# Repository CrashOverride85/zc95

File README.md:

# ZC95

**Note**: This repo has submodules, so if cloning, it's best to use the recursive option.

## Introduction
The ZC95 is a DIY four channel EStim box with similar output design and feel to the MK312-BT (which in turn is a clone of the ET-312B).

![zc95]

The box is primarily intended for standalone use (i.e. not used whilst connected to phone/laptop/tablet), but can be controlled remotely via a Python GUI, and run Lua scripts that have been uploaded to it over serial or WiFi.

Main features:
- 4 isolated channels 
- [Audio input](./docs/AudioInput-Operation.md) - line level for estim tracks or microphone input (selectable via menu)
- [Many inbuilt patterns](./docs/Patterns.md) - around 14, not counting audio and more esoteric stuff
- Custom patterns can be written in [Lua](./docs/LuaNotes.md)
- Two stereo 3.5mm trigger input sockets, allowing for up to 4 external inputs (e.g. remote buttons, foot pedals, etc.)
- Support for many [BLE remote/camera buttons](./docs//BluetoothPeripherals.md), e.g. to trigger output when the button is pressed
- [Remote control](./docs/RemoteAccess.md) over WiFi or serial using a python app
- Allows limited control of a certain type of 433MHz shock collar
- Somewhat experimental [BLE steaming](./docs/BleStreaming.md) - allows for per-pulse level control from laptop or other device, with an example in python
- An accessory port with 3 output lines that can be controlled from Lua scripts, to allow interacting with other devices

Technical details:
- Has been designed with the JLC PCB assembly service in mind, and is mostly an SMD design with a few though hole parts
- Uses 2x Raspberry Picos
- Firmware is open source and mostly C++, and makes use of many [3rd party libraries](./docs/Credits.md)
- 26650 cell for power
- KiCad project files included in repo, not just gerbers
- Audio input includes microphone preamp that can be toggled via menu, along with variable gain
- Consists of 3 PCBs:
   * Front panel - no traces, just text / mounting holes
   * Front panel controls - 4x POTs and associated ADC, 1x rotary encoder and 6 serial RGB LEDs. Designed for production using the SMT assembly service at JLCPCB, with a handful of extra through hole parts also requiring hand soldering.
   * Main board - power supply / charging, pattern generation, button input, output signal generation, audio input
- Case is either an off the shelf Hammond 1598DBK (larger), or a 3D printed case (step/stl files provided)

## [Build guide](docs/Build.md)

## [Schematics](schematics/)

## [Gerbers](pcb/)

## [Compiled firmware](https://github.com/CrashOverride85/zc95/releases/)

## [Operation notes](docs/Operation.md)

## [Pattern guide](docs/Patterns.md)

## [Lua scripting notes](docs/LuaNotes.md)

## [Notes on building source](docs/SourceBuildNotes.md)

## [Credits](docs/Credits.md)

# Miscellaneous  
## History
The ZC95 is very heavily inspired by the MK312-BT, which is a reversed engineered version of the ET-312. The original repo for that project is long gone, but there is a fork [here](https://github.com/CrashOverride85/mk312-bt).

The [ZC95 mk1](https://github.com/CrashOverride85/zc95/tree/MKI) was made public in late 2021, and had a similar form factor to the MK312. That version has been built successfully by many.

The [ZC95 mk1](https://github.com/CrashOverride85/zc95/tree/MKI) had the output stage on a separate PCB. It's no longer part of the zc95 build, but could still be built and used to add 4 channel estim output to an Arduino (with notes for & tested with an ESP32).
The PCB / BoM / build notes for it are [here](./misc/OutputBoard/README.md).

## MKI vs. MKII
These are the main changes from the MKI to MKII:

 - Much smaller - the mainboard is less than half the size
 - Output, Audio and main board are now combined
 - USB-C charger input instead of 15v barrel jack
 - 26650 cell instead of 12v SLA battery (similar capacity)
 - "Aux" socket swapped for separate "Serial" and "Audio" sockets
 - Output sockets changed from 2.5mm to 3.5mm
 - Serial selectable (via jumpers) between 3.3v TTL and RS232
 - Display no longer briefly flashes white on power on
 - Removed: 12v output on accessory port

## Support, feedback, etc.
The ZC95 project is provided 'as is' without warranty of any kind, either express or implied. The project is provided for your use at your own risk.

Having said that, if you run into difficulties or have questions, the two best places to try are:
- Github [discussions](https://github.com/CrashOverride85/zc95/discussions) or [issues](https://github.com/CrashOverride85/zc95/issues)
- The ZC95 channel on [Joanne's E-Stim Community discord](https://discord.gg/HbGKY2t), see Estim control boxes -> zc95
  - I'd highly recommend joining this discord server anyway, the zc95 chanel is a _tiny_ part of what's there

## Other projects
Other related projects that are worth checking out:

- [NeoDK](https://github.com/Onwrikbaar/NeoDK) - Advanced electrostimulation machine development kit. In active development, and also has a chanel on [Joanne's E-Stim Community discord](https://discord.gg/HbGKY2t)

- MK-312BT - Project the ZC95 was inspired by, and shares lot in common with (original repo gone, but there are many [forks](https://github.com/CrashOverride85/mk312-bt))

- [WT-312](https://github.com/WendyTeslaburger/WT-312) - 312 style driver, intended for integration into other projects

- [FOC-Stim](https://github.com/diglet48/FOC-Stim) - In development, checkout the foc-stim channel on [Joanne's E-Stim Community discord](https://discord.gg/HbGKY2t) for the latest

# TODO
## Firmware
   - Triphase support from Lua 
   - Allow Lua scripts to interact with shock collars
   - Combo pattern? Having, e.g., waves on channels 1+2 plus something like TENS on 3+4 would be good
   - Save pattern settings on exit?
   - Disable when plugged in / switch to charging screen (maybe a setting in the menu to disable)
   - Accessory port doesn't do much - just 3 output lines. There's a serial interface there too, which could be exposed in the Lua environment

## Hardware
   - Improved 3D printed case?

## Known issues
   - Will charge faster if switched on when plugged in, and not switched off for at least 10 seconds (or just left on)
   - Sometimes when finished charging (battery icon showing solid green), the battery percentage will only show ~95% despite being fully charged. Should be fixed in a future firmware version. 

[zc95]: docs/images/powered_up.jpg "Assembled ZC95"

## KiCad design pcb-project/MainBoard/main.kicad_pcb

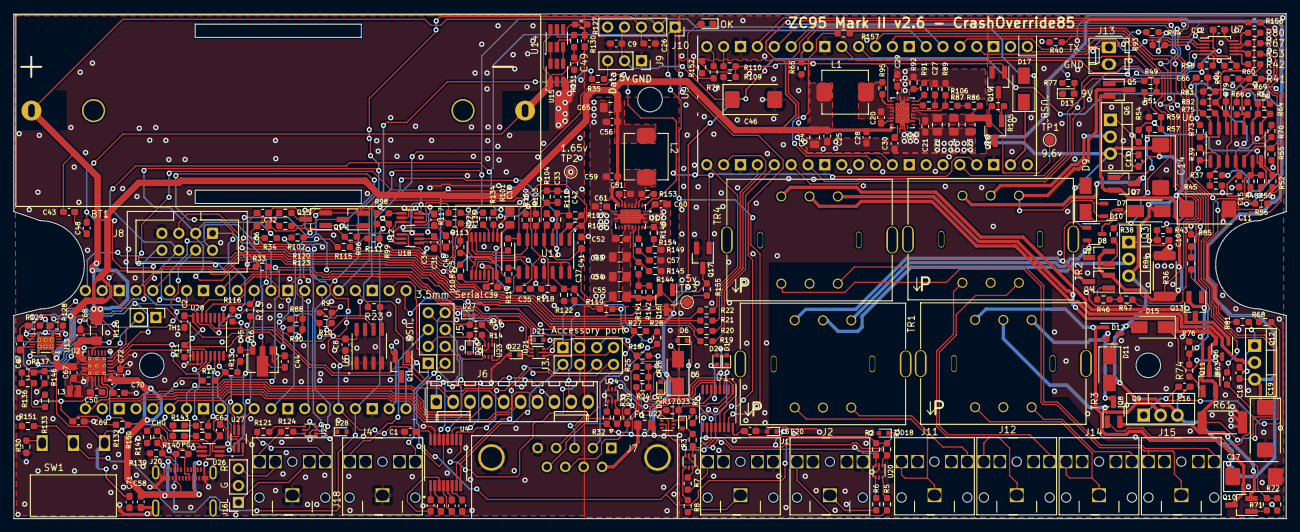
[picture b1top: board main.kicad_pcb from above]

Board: 2 copper layers, 191.5 x 76.0 mm, 334 parts (1 on the bottom side), 263 nets.

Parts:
BT1: 26650 Cell; BH-26650-A5BJ001
C1, C2, C5, C21, C26, C32, C36, C37, C39, C41, C42, C43, C44, C45, C48, C52: 1uF; C_0603_1608Metric_Pad1.08x0.95mm_HandSolder
C3, C4, C6, C7, C8, C10, C12, C13, C15, C16, C18, C20, C28, C30, C31, C34, C49, C51, C59, C61: 100nF; C_0603_1608Metric_Pad1.08x0.95mm_HandSolder
C9, C25, C40, C56, C66, C67, C68, C70, C72: 10uF; C_0603_1608Metric_Pad1.08x0.95mm_HandSolder
C11, C14, C17, C19, C46: 220uF; CP_EIA-7343-43_Kemet-X_Pad2.25x2.55mm_HandSolder
C22, C23, C24, C38, C53, C54, C55, C64, C65: 22uF; C_0805_2012Metric_Pad1.18x1.45mm_HandSolder
C27, C57, C62: 10nF; C_0603_1608Metric_Pad1.08x0.95mm_HandSolder
C29, C33, C35, C60: 3.3nF; C_0603_1608Metric_Pad1.08x0.95mm_HandSolder
C47: 0.47uF; C_0603_1608Metric_Pad1.08x0.95mm_HandSolder
C50: 47nF; C_0603_1608Metric_Pad1.08x0.95mm_HandSolder
C58, C71: DNP; C_0603_1608Metric_Pad1.08x0.95mm_HandSolder
C63: DNP; R_0805_2012Metric_Pad1.20x1.40mm_HandSolder
C69: 4.7uF; C_0603_1608Metric_Pad1.08x0.95mm_HandSolder
D1, D6, D18, D20, D21, D22, D23, D24, D25, D26, D27, D28: BZX584C3V6; D_SOD-523
D3: PG; LED_0603_1608Metric_Pad1.05x0.95mm_HandSolder
D4: CHRG; LED_0603_1608Metric_Pad1.05x0.95mm_HandSolder
D5: 1SMA4734A; D_SMA
D7, D9, D11, D15: SMAJ13A; D_SMA
D8, D10, D12, D16: BAV23CL; SOT-23-3
D13: 9v; LED_0603_1608Metric_Pad1.05x0.95mm_HandSolder
D14: OK; LED_0603_1608Metric_Pad1.05x0.95mm_HandSolder
D17: SS34; D_SMA
F1: 500mA; Fuse_0805_2012Metric_Pad1.15x1.40mm_HandSolder
J1: TRG1; PJ-3062-CO
J2: TRG2; PJ-3062-CO
J3, J5: Conn_02x04_Odd_Even; PinSocket_2x04_P2.54mm_Vertical
J4, J18: AudioJack3_SwitchTR; PJ-3062-CO
J6: LCD; Molex_KK-254_AE-6410-10A_1x10_P2.54mm_Vertical
J7: ACC Port; DSUB-9_Female_Horizontal_P2.77x2.84mm_EdgePinOffset7.70mm_H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
J8: FrontPanel; IDC-Header_2x04_P2.54mm_Vertical
J9: 433TX; PinSocket_1x03_P2.54mm_Vertical
J10: I2C; PinSocket_1x05_P2.54mm_Vertical
J11: CHAN1; PJ-3062-CO
J12: CHAN2; PJ-3062-CO
J13: Conn_01x02; Molex_KK-254_AE-6410-02A_1x02_P2.54mm_Vertical
J14: CHAN3; PJ-3062-CO
J15: CHAN4; PJ-3062-CO
J16: AudioIn; PinSocket_1x03_P2.54mm_Vertical
J20: USB_C_Receptacle; 1054500101
L1, L2: 1.5uH; FXL0630
L3: FTC201610S1R0MBCA; FTC201610S
Q1, Q14, Q15, Q16, Q18: AO3401A; SOT-23_Handsoldering
Q2, Q4, Q5, Q7, Q8, Q10, Q11, Q13, Q17, Q19: AO3400A; SOT-23_Handsoldering
Q3, Q6, Q9, Q12: IRF9Z24NPBF; TO-220-3_Vertical
R1, R2, R3, R4, R11, R15, R17, R18, R23, R24, R25, R26, R33, R34, R38, R43, R46, R49, R54, R57, R63, R68, R71, R74, R77, R81, R84, R101, R103, R105, R109, R114, R117, R125, R128, R129, R132, R136, R137, R146, R151, R152, R155, R156, R157: 10k; R_0603_1608Metric_Pad0.98x0.95mm_HandSolder
R5, R6, R7, R8, R9, R14, R16, R19, R20, R21, R22, R27, R28, R29, R30, R31, R32, R35, R88, R110, R121, R124, R127, R134, R135: 100R; R_0603_1608Metric_Pad0.98x0.95mm_HandSolder
R10, R90, R120, R123, R138, R143: 2k2; R_0603_1608Metric_Pad0.98x0.95mm_HandSolder
R12, R13, R37, R39, R40, R42, R45, R47, R48, R50, R51, R53, R56, R58, R59, R60, R62, R64, R65, R67, R70, R72, R73, R75, R76, R80, R83, R85, R96, R98, R104, R108, R111, R112, R116, R118, R119, R122, R142, R144, R147, R150: 100k; R_0603_1608Metric_Pad0.98x0.95mm_HandSolder
R36, R61: 0.5R; R_2512_6332Metric_Pad1.40x3.35mm_HandSolder
R41, R44, R52, R55, R66, R69, R79, R82, R91, R92, R97, R99, R148, R149: 150k; R_0603_1608Metric_Pad0.98x0.95mm_HandSolder
R78: 1.5k; R_0603_1608Metric_Pad0.98x0.95mm_HandSolder
R86, R95, R141, R153: 330K; R_0603_1608Metric_Pad0.98x0.95mm_HandSolder
R87, R89, R145: 56k; R_0603_1608Metric_Pad0.98x0.95mm_HandSolder
R93, R94, R100, R106, R107, R113, R133, R154: 4k7; R_0603_1608Metric_Pad0.98x0.95mm_HandSolder
R102, R115, R130, R131: 1k; R_0603_1608Metric_Pad0.98x0.95mm_HandSolder
R126: 0.01R; R_1206_3216Metric_Pad1.30x1.75mm_HandSolder
R139, R140: 5.1k; R_0603_1608Metric_Pad0.98x0.95mm_HandSolder
SW1: SW_SPDT; SS-12D06L5
TH1: Thermistor_NTC; PinHeader_1x02_P2.54mm_Vertical
TP1: TestPoint_9.6v; TestPoint_Pad_D1.5mm
TP2: TestPoint_1.65v; TestPoint_Pad_D1.5mm
TP3: TestPoint_5v; TestPoint_Pad_D1.5mm
TR1, TR2, TR3, TR4: 42TL004-RC; 42TL+U
U1, U28: TCA9534; TSSOP-16_4.4x5mm_P0.65mm
U2: BQ25601; Texas_S-PWQFN-N24_EP2.7x2.7mm_ThermalVias
U3, U9: Pico; RPi_Pico_SMD_TH
U4: MAX3232EEAE+T; SOP65P777X199-16N
U5: AT24C04CDRG; SOP-8_3.76x4.96mm_P1.27mm
U6, U11: LM324; SOIC-14_3.9x8.7mm_P1.27mm
U7: MCP4728; MSOP-10_3x3mm_P0.5mm
U8, U17: TPS61088; IC_TPS61088RHLR
U10: MCP4651; TSSOP-14_4.4x5mm_P0.65mm
U12, U18, U26, U27: SN74LVC1G3157DCKR; SOT-363_SC-70-6_Handsoldering
U13: BQ27441-G1; Texas_S-PDSO-N12
U14: HY2111-GB; SOT-23-6_Handsoldering
U15: FS8205A; SOT-23-6_Handsoldering
U16: HT7533-1; SOT-89-3
U19, U20, U21, U22, U23, U24, U25: USBLC6-2P6; SOT-666

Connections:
1.65v: C33.2, C35.2, R97.1, R99.1, R100.2, R104.1, R107.2, R111.1, R112.1, R113.2, R118.1, TP2.1, U11.13 (-), U11.14
3.5v: C25.1, C28.1, C56.1, C59.1, C63.1, C64.2, C65.1, C67.1, C71.1, D3.2 (A), D4.2 (A), D17.2 (A), L1.1, L2.1, L3.2, Q1.3 (D), SW1.1 (A), U2.15 (SYS), U2.16 (SYS), U8.9 (VIN), U17.9 (VIN)
3v3: C1.1, C2.2, C5.2, C8.2, C26.1, C62.1, J8.3, J10.3, R1.1, R2.1, R3.1, R4.1, R10.2, R11.1, R15.1, R17.1, R18.2, R24.1, R25.1, R26.1, R33.2, R34.2, R90.2, U1.16 (VDD), U3.36 (3V3), U4.16 (VCC), U5.8 (VCC), U26.5 (VCC), U27.5 (VCC), U28.16 (VDD)
3v3_2: C12.1, R58.2, R93.2, R94.2, U7.1 (VDD), U9.36 (3V3)
3v3_LDO: C45.2, Q14.2 (S), Q15.2 (S), R116.2, R119.2, U16.3 (VOUT)
5v: C9.1, C31.2, C34.2, C38.1, C39.2, C40.1, C41.2, C42.1, C44.2, C46.1, C66.1, D5.1 (K), F1.1, J6.9, J8.5, J9.2, J10.4, Q16.3 (D), R37.2, R48.1, R62.2, R73.2, R125.1, U10.14 (VDD), U11.4 (V+), U12.5 (VCC), U16.2 (VIN), U18.5 (VCC)
9v_EN: Q19.1 (G), R109.2, R110.1, R152.1, U8.2 (EN)
232_UART0_RX: J5.2, U4.13 (R1IN)
232_UART0_RX_TTL: J5.4, U4.12 (R1OUT)
232_UART0_TX: J5.6, U4.14 (T1OUT)
232_UART0_TX_TTL: J5.8, U4.11 (T1IN)
232_UART1_RX: J3.2, U4.8 (R2IN)
232_UART1_TX: J3.6, U4.7 (T2OUT)
433TX: R35.1, U3.5 (GPIO3)
+9v: C10.2, C11.1, C13.2, C14.1, C15.1, C16.2, C17.1, C18.2, C19.1, D7.2 (A2), D9.2 (A2), D11.2 (A2), D15.2 (A2), Q3.3 (S), Q6.3 (S), Q9.3 (S), Q12.3 (S), Q18.3 (D), R41.2, R52.2, R66.2, R77.2, R79.2, U6.4 (V+)
/-> RX_ACC ->: J3.1, R28.2
/-> TX_ACC: J3.5, R27.2
/Output/CS: R20.1, U9.22 (GPIO17)
/Output/MISO: R19.1, U9.25 (GPIO19)
/Output/MOSI: R22.1, U9.21 (GPIO16)
/Output/SCK: R21.1, U9.24 (GPIO18)
/Power/PACKP: BT1.1 (+), C43.1, R126.1, R127.1, U13.6 (BAT), U13.8 (SRP)
ACC-IO-1: D25.1 (K), U1.4 (P0), U24.6 (I/O1)
ACC-IO-2: D24.1 (K), U1.5 (P1), U24.4 (I/O2)
ACC-IO-3: D23.1 (K), U1.6 (P2), U22.6 (I/O1)
ADC0: Q2.2 (S), Q4.2 (S), Q5.2 (S), Q7.2 (S), R36.1, R157.1
ADC1: Q8.2 (S), Q10.2 (S), Q11.2 (S), Q13.2 (S), R61.1, R156.1
AUDIO_IN_L: C32.1, R98.1, R112.2, U11.3 (+)
AUDIO_IN_R: C36.1, R96.1, R111.2
AUDIO_L: R102.1, U3.32 (GPIO27_ADC1)
AUDIO_R: R115.1, U3.34 (GPIO28_ADC2)
BAT+: C68.1, R126.2, R128.1, U2.13 (BAT), U2.14 (BAT), U13.7 (SRN)
C1-GA: R38.2, R40.1, U9.9 (GPIO6)
C1-GB: R46.2, R47.1, U9.10 (GPIO7)
C2-GA: R49.2, R51.1, U9.11 (GPIO8)
C2-GB: R57.2, R59.1, U9.12 (GPIO9)
C3-GA: R63.2, R65.1, U9.14 (GPIO10)
C3-GB: R71.2, R72.1, U9.15 (GPIO11)
C4-GA: R74.2, R76.1, U9.16 (GPIO12)
C4-GB: R84.2, R85.1, U9.17 (GPIO13)
CELL-: BT1.2 (-), C47.1, C48.2, C49.2, R129.2, U13.3 (VSS), U13.13 (PAD), U14.6 (VSS), U15.1
CHRG: R143.1, U2.4 (STAT), U28.5 (P1)
DAC-C1: R42.1, U7.6 (VOUTA)
DAC-C2: R53.1, U7.7 (VOUTB)
DAC-C3: R67.1, U7.8 (VOUTC)
DAC-C4: R80.1, U7.9 (VOUTD)
FP_INT1: J8.1, R33.1, U3.15 (GPIO11)
FP_INT2: J8.2, R34.1, U3.9 (GPIO6)
GND: C1.2, C2.1, C5.1, C6.2, C7.2, C8.1, C9.2, C11.2, C12.2, C14.2, C15.2, C17.2, C19.2, C21.1, C22.2, C23.2, C24.2, C25.2, C26.2, C27.1, C28.2, C29.2, C30.1, C31.1, C34.1, C37.1, C38.2, C39.1, C40.2, C41.1, C42.2, C44.1, C45.1, C46.2, C52.1, C53.2, C54.2, C55.2, C56.2, C57.1, C58.2, C59.2, C60.2, C61.1, C62.2, C63.2, C64.1, C65.2, C66.2, C67.2, C68.2, C69.2, C70.2, C71.2, C72.2, D1.2 (A), D5.2 (A), D6.2 (A), D13.1 (K), D14.1 (K), D18.2 (A), D20.2 (A), D21.2 (A), D22.2 (A), D23.2 (A), D24.2 (A), D25.2 (A), D26.2 (A), D27.2 (A), D28.2 (A), J1.T, J2.T, J4.S, J6.10, J7.0 (PAD), J7.5, J8.7, J9.1, J10.5, J13.2, J16.2, J18.S, J20.A1 (GND), J20.A12 (GND), J20.B1 (GND), J20.B12 (GND), J20.S1 (SHIELD), Q17.2 (S), Q19.2 (S), R13.2, R23.1, R30.1, R36.2, R40.2, R44.1, R45.1, R47.2, R51.2, R55.1, R56.2, R59.2, R60.2, R61.2, R65.2, R69.1, R70.1, R72.2, R76.2, R82.1, R83.1, R85.2, R89.2, R92.2, R109.1, R122.2, R131.2, R139.2, R140.2, R145.2, R146.1, R149.2, R151.1, R152.2, TH1.1, U1.1 (A0), U1.3 (A2), U1.8 (GND), U2.9 (~CE), U2.17 (GND), U2.18 (GND), U2.25 (GND), U3.3 (GND), U3.8 (GND), U3.13 (GND), U3.18 (GND), U3.23 (GND), U3.28 (GND), U3.33 (AGND), U3.38 (GND), U4.15 (GND), U5.1 (A0), U5.2 (A1), U5.3 (A2), U5.4 (GND), U5.7 (WP), U6.11 (V-), U7.10 (VSS), U8.13 (MODE), U8.20 (AGND), U8.21 (PGND), U9.3 (GND), U9.8 (GND), U9.13 (GND), U9.18 (GND), U9.23 (GND), U9.28 (GND), U9.38 (GND), U10.1 (A0), U10.4 (VSS), U10.11 (N/C), U10.13 (A1), U11.11 (V-), U12.2 (GND), U15.3, U16.1 (GND), U17.20 (AGND), U17.21 (PGND), U18.2 (GND), U19.2 (GND), U20.2 (GND), U21.2 (GND), U22.2 (GND), U23.2 (GND), U24.2 (GND), U25.2 (GND), U26.2 (GND), U27.2 (GND), U28.2 (A1), U28.3 (A2), U28.8 (GND)
I2C_SCL_PER: R94.1, U7.2 (SCL), U9.5 (GPIO3)
I2C_SDA_PER: R93.1, U7.3 (SDA), U9.4 (GPIO2)
IO-EXP1-INT: R15.2, U3.10 (GPIO7), U28.13 (~INT)
IO-EXP2-INT: R18.1, U1.13 (~INT), U3.27 (GPIO21)
LCD-LITE: J6.1, R23.2, U3.4 (GPIO2)
LCD-RESET: J6.8, U28.12 (P7)
LDAC: R60.1, U7.4 (~LDAC), U9.27 (GPIO21)
LED-DATA: J8.8, U3.14 (GPIO10)
MCU_UART0_RX: U3.2 (GPIO1), U23.4 (I/O2)
MCU_UART0_TX: U3.1 (GPIO0), U23.6 (I/O1)
MCU_UART1_RX: D21.1 (K), U3.12 (GPIO9), U21.4 (I/O2)
MCU_UART1_RX_TTL: J3.4, U4.9 (R2OUT)
MCU_UART1_TX: D22.1 (K), U3.11 (GPIO8), U21.6 (I/O1)
MCU_UART1_TX_TTL: J3.8, U4.10 (T2IN)
MIC_PREAMP_EN: U12.6 (S), U18.6 (S), U28.9 (P4)
MIC_PREAMP_OUT: R108.2, U11.1, U18.1 (B2)
MIC_PWR_DIS: Q14.1 (G), Q15.1 (G), R116.1, U28.10 (P5)
unnamed: C3.1, U4.1 (C1+)
unnamed: C3.2, U4.3 (C1-)
unnamed: C4.1, U4.4 (C2+)
unnamed: C4.2, U4.5 (C2-)
unnamed: C6.1, U4.2 (VS+)
unnamed: C7.1, U4.6 (VS-)
unnamed: C10.1, Q3.1 (G), R43.1
unnamed: C13.1, Q6.1 (G), R54.1
unnamed: C16.1, Q9.1 (G), R68.1
unnamed: C18.1, Q12.1 (G), R81.1
unnamed: C20.1, L1.2, R95.1, U8.4 (SW), U8.5 (SW), U8.6 (SW), U8.7 (SW)
unnamed: C20.2, U8.8 (BOOT)
unnamed: C21.2, C22.1, C23.1, C24.1, Q18.2 (S), R86.1, R105.2, TP1.1, U8.14 (VOUT), U8.15 (VOUT), U8.16 (VOUT)
unnamed: C27.2, R106.1
unnamed: C29.1, U8.1 (VCC)
unnamed: C30.2, U8.10 (SS)
unnamed: C32.2, R123.2, U25.3 (I/O2)
unnamed: C33.1, R103.1, R104.2, U11.5 (+)
unnamed: C35.1, R117.1, R118.2, U11.10 (+)
unnamed: C36.2, R120.2, U25.1 (I/O1)
unnamed: C37.2, R119.1, R122.1, U11.12 (+)
unnamed: C43.2, C48.1
unnamed: C47.2, U13.5 (VDD)
unnamed: C49.1, R127.2, U14.5 (VDD)
unnamed: C50.1, L3.1, U2.19 (SW), U2.20 (SW)
unnamed: C50.2, U2.21 (BTST)
unnamed: C51.1, L2.2, R153.1, U17.4 (SW), U17.5 (SW), U17.6 (SW), U17.7 (SW)
unnamed: C51.2, U17.8 (BOOT)
unnamed: C52.2, C53.1, C54.1, C55.1, Q16.2 (S), R141.2, R142.1, R155.2, TP3.1, U17.14 (VOUT), U17.15 (VOUT), U17.16 (VOUT)
unnamed: C57.2, R154.1
unnamed: C58.1, C72.1, J20.A4 (VBUS), J20.A9 (VBUS), J20.B4 (VBUS), J20.B9 (VBUS), R12.1, U2.1 (VAC), U2.24 (VBUS)
unnamed: C60.1, U17.1 (VCC)
unnamed: C61.2, U17.10 (SS)
unnamed: C70.1, U2.23 (PMID)
unnamed: D1.1 (K), R4.2, U1.12 (P7), U19.3 (I/O2)
unnamed: D3.1 (K), R138.2
unnamed: D4.1 (K), R143.2
unnamed: D6.1 (K), R3.2, U1.11 (P6), U19.1 (I/O1)
unnamed: D7.1 (A1), D8.3 (K)
unnamed: D8.1 (A), Q4.3 (D), TR1.3
unnamed: D8.2 (A), Q2.3 (D), TR1.1
unnamed: D10.1 (A), Q7.3 (D), TR2.3
unnamed: D10.2 (A), Q5.3 (D), TR2.1
unnamed: D9.1 (A1), D10.3 (K)
unnamed: D11.1 (A1), D12.3 (K)
unnamed: D12.1 (A), Q10.3 (D), TR3.3
unnamed: D12.2 (A), Q8.3 (D), TR3.1
unnamed: D13.2 (A), R77.1
unnamed: D14.2 (A), R78.1
unnamed: D15.1 (A1), D16.3 (K)
unnamed: D16.1 (A), Q13.3 (D), TR4.3
unnamed: D16.2 (A), Q11.3 (D), TR4.1
unnamed: D17.1 (K), U9.39 (VSYS)
unnamed: D18.1 (K), R2.2, U1.10 (P5), U20.3 (I/O2)
unnamed: D20.1 (K), R1.2, U1.9 (P4), U20.1 (I/O1)
unnamed: D26.1 (K), J5.3, R14.2
unnamed: D27.1 (K), J5.7, R16.2
unnamed: D28.1 (K), U25.5 (VBUS)
unnamed: F1.2, J7.6
unnamed: J1.R, R7.1
unnamed: J1.S, R8.2
unnamed: J2.R, R5.2
unnamed: J2.S, R6.1
unnamed: J3.3, U21.3 (I/O2)
unnamed: J3.7, U21.1 (I/O1)
unnamed: J4.R, J5.5
unnamed: J4.T, J5.1
unnamed: J7.2, R28.1
unnamed: J7.3, R27.1
unnamed: J7.4, R25.2, R31.2
unnamed: J7.8, R24.2, R29.2
unnamed: J7.9, R26.2, R32.2
unnamed: J9.3, R35.2
unnamed: J11.R, J11.S, TR1.4
unnamed: J11.T, TR1.6
unnamed: J12.R, J12.S, TR2.4
unnamed: J12.T, TR2.6
unnamed: J14.R, J14.S, TR3.4
unnamed: J14.T, TR3.6
unnamed: J15.R, J15.S, TR4.4
unnamed: J15.T, TR4.6
unnamed: J16.1, J18.TN
unnamed: J16.3, J18.RN
unnamed: J18.R, R124.1
unnamed: J18.T, R121.1
unnamed: Q1.1 (G), U3.40 (VBUS)
unnamed: Q1.2 (S), U3.39 (VSYS)
unnamed: Q2.1 (G), R38.1
unnamed: Q3.2 (D), TR1.2
unnamed: Q4.1 (G), R46.1
unnamed: Q5.1 (G), R49.1
unnamed: Q6.2 (D), TR2.2
unnamed: Q7.1 (G), R57.1
unnamed: Q8.1 (G), R63.1
unnamed: Q9.2 (D), TR3.2
unnamed: Q10.1 (G), R71.1
unnamed: Q11.1 (G), R74.1
unnamed: Q12.2 (D), TR4.2
unnamed: Q13.1 (G), R84.1
unnamed: Q14.3 (D), R120.1
unnamed: Q15.3 (D), R123.1
unnamed: Q16.1 (G), Q17.3 (D), R155.1
unnamed: Q18.1 (G), Q19.3 (D), R105.1
unnamed: R5.1, U20.6 (I/O1)
unnamed: R6.2, U20.4 (I/O2)
unnamed: R7.2, U19.6 (I/O1)
unnamed: R8.1, U19.4 (I/O2)
unnamed: R9.2, R10.1, U3.6 (GPIO4)
unnamed: R11.2, U28.1 (A0)
unnamed: R14.1, U23.3 (I/O2)
unnamed: R16.1, U23.1 (I/O1)
unnamed: R17.2, U1.2 (A1)
unnamed: R19.2, U3.16 (GPIO12)
unnamed: R20.2, U3.17 (GPIO13)
unnamed: R21.2, U3.19 (GPIO14)
unnamed: R22.2, U3.20 (GPIO15)
unnamed: R29.1, U22.1 (I/O1)
unnamed: R30.2, SW1.3 (C)
unnamed: R31.1, U24.3 (I/O2)
unnamed: R32.1, U24.1 (I/O1)
unnamed: R37.1, R39.2, R45.2, U6.2 (-)
unnamed: R39.1, R43.2, U6.1
unnamed: R41.1, R42.2, R44.2, U6.3 (+)
unnamed: R48.2, R50.1, R56.1, U6.6 (-)
unnamed: R50.2, R54.2, U6.7
unnamed: R52.1, R53.2, R55.2, U6.5 (+)
unnamed: R62.1, R64.2, R70.2, U6.9 (-)
unnamed: R64.1, R68.2, U6.8
unnamed: R66.1, R67.2, R69.2, U6.10 (+)
unnamed: R73.1, R75.2, R83.2, U6.13 (-)
unnamed: R75.1, R81.2, U6.14
unnamed: R79.1, R80.2, R82.2, U6.12 (+)
unnamed: R86.2, R87.2
unnamed: R87.1, R89.1, U8.17 (FB)
unnamed: R88.2, R90.1, U3.7 (GPIO5)
unnamed: R91.1, U8.19 (ILIM)
unnamed: R91.2, R92.1
unnamed: R95.2, U8.3 (FSW)
unnamed: R96.2, R97.2, U12.3 (B1)
unnamed: R98.2, R99.2, U12.1 (B2), U18.3 (B1)
unnamed: R100.1, U10.7 (P1A), U11.6 (-)
unnamed: R101.1, R102.2, U11.7
unnamed: R101.2, U10.6 (P1W)
unnamed: R103.2, U18.4 (A)
unnamed: R106.2, U8.18 (COMP)
unnamed: R107.1, R108.1, U11.2 (-)
unnamed: R110.2, U9.19 (GPIO14)
unnamed: R113.1, U10.8 (P0A), U11.9 (-)
unnamed: R114.1, R115.2, U11.8
unnamed: R114.2, U10.9 (P0W)
unnamed: R117.2, U12.4 (A)
unnamed: R121.2, U25.4 (I/O2)
unnamed: R124.2, U25.6 (I/O1)
unnamed: R125.2, U10.12 (A2)
unnamed: R128.2, U13.12 (GPOUT)
unnamed: R129.1, U13.10 (BIN)
unnamed: R130.1, U14.2 (CS)
unnamed: R130.2, R131.1
unnamed: R132.2, U2.2 (PSEL)
unnamed: R133.1, R136.2, TH1.2, U2.11 (TS)
unnamed: R134.1, U10.2 (SCL)
unnamed: R135.1, U10.3 (SDA)
unnamed: R136.1, R137.1
unnamed: R137.2, R146.2
unnamed: R141.1, R142.2, R144.2
unnamed: R144.1, R145.1, U17.17 (FB)
unnamed: R147.1, U26.3 (B1)
unnamed: R148.1, U17.19 (ILIM)
unnamed: R148.2, R149.1
unnamed: R150.1, U26.1 (B2)
unnamed: R153.2, U17.3 (FSW)
unnamed: R154.2, U17.18 (COMP)
unnamed: R156.2, U9.32 (GPIO27_ADC1)
unnamed: R157.2, U9.31 (GPIO26_ADC0)
unnamed: U14.1 (OD), U15.6
unnamed: U14.3 (OC), U15.4
unnamed: U26.4 (A), U27.3 (B1)
OK_LED: R78.2, U9.20 (GPIO15)
PWR_EN: Q17.1 (G), R151.2, SW1.2 (B), U3.37 (3V3_EN), U9.37 (3V3_EN), U17.2 (EN)
RDY: R58.1, U7.5 (RDY/~BSY), U9.26 (GPIO20)
REGN: C69.1, R132.1, R133.2, U2.22 (REGN)
SCL: J8.6, J10.1, R88.1, R134.2, U1.14 (SCL), U2.5 (SCL), U5.6 (SCL), U9.7 (GPIO5), U13.2 (SCL), U28.14 (SCL)
SDA: J8.4, J10.2, R9.1, R135.2, U1.15 (SDA), U2.6 (SDA), U5.5 (SDA), U9.6 (GPIO4), U13.1 (SDA), U28.15 (SDA)
SERIAL_TX: J13.1, U9.1 (GPIO0)
SPI-CS-LCD: J6.5, U3.22 (GPIO17)
SPI-CS-SD: J6.6, U3.29 (GPIO22)
SPI-DC: J6.7, U3.26 (GPIO20)
SPI-MISO: J6.2, U3.21 (GPIO16)
SPI-MOSI: J6.4, U3.25 (GPIO19)
SPI-SCK: J6.3, U3.24 (GPIO18)
STDBY: R138.1, U2.3 (~PG), U28.4 (P0)
USB-CC1: J20.A5 (CC1), R139.1, R150.2
USB-CC2: J20.B5 (CC2), R140.1, R147.2
USB-SENSE: U3.31 (GPIO26_ADC0), U27.4 (A)
USB-VBUS: R12.2, R13.1, U27.1 (B2)
USB_SENSE1: U26.6 (S), U28.6 (P2)
USB_SENSE2: U27.6 (S), U28.7 (P3)

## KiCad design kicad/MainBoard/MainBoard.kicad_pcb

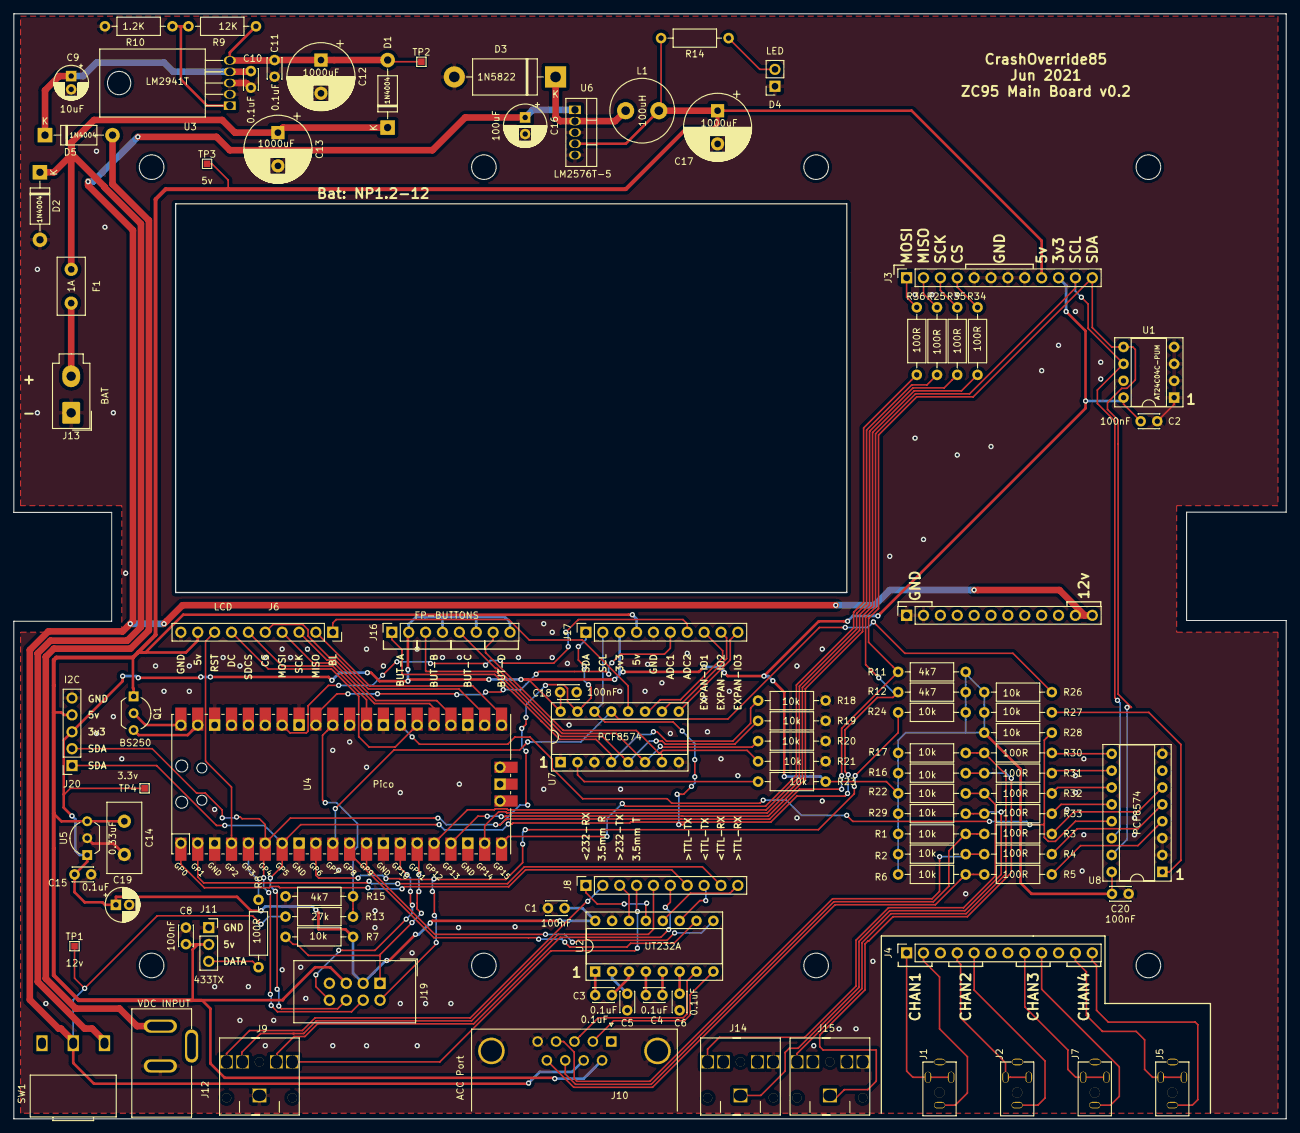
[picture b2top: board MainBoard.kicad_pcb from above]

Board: 2 copper layers, 191.5 x 166.3 mm, 96 parts (0 on the bottom side), 93 nets.

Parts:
C1, C2, C8, C18, C20: 100nF; C_Disc_D3.0mm_W2.0mm_P2.50mm
C3, C4, C5, C6, C10, C11, C15: 0.1uF; C_Disc_D3.0mm_W2.0mm_P2.50mm
C9, C19: 10uF; CP_Radial_D5.0mm_P2.00mm
C12, C13, C17: 1000uF; CP_Radial_D10.0mm_P5.00mm
C14: 0.33uF; C_Disc_D10.5mm_W5.0mm_P5.00mm
C16: 100uF; CP_Radial_D6.3mm_P2.50mm
D1, D2, D5: 1N4004; D_DO-41_SOD81_P10.16mm_Horizontal
D3: 1N5822; D_DO-201AD_P15.24mm_Horizontal
D4: LED; PinSocket_1x02_P2.54mm_Vertical
F1: 1A; Fuse_Littelfuse_395Series
J1: CHAN1; PJ-2100B-4A
J2: CHAN2; PJ-2100B-4A
J3: OUTPUT_BOARD_IO; PinSocket_1x12_P2.54mm_Vertical
J4: OUTPUT_BOARD_FP; PinSocket_1x12_P2.54mm_Vertical
J5: CHAN4; PJ-2100B-4A
J6: LCD; PinSocket_1x10_P2.54mm_Vertical
J7: CHAN3; PJ-2100B-4A
J8: EXPAN1; PinSocket_1x10_P2.54mm_Vertical
J9: AudioJack3_SwitchTR; PJ-3062-CO
J10: ACC Port; DSUB-9_Female_Horizontal_P2.77x2.84mm_EdgePinOffset7.70mm_H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
J11: 433TX; PinSocket_1x03_P2.54mm_Vertical
J12: VDC INPUT; DC-005-2.5A-2.0
J13: BAT; Molex_Mini-Fit_Jr_5566-02A_2x01_P4.20mm_Vertical
J14: TRG1; PJ-3062-CO
J15: TRG2; PJ-3062-CO
J16: FP-BUTTONS; PinSocket_1x08_P2.54mm_Vertical
J17: EXPAN2; PinSocket_1x10_P2.54mm_Vertical
J18: OUTPUT_BOARD_POWER; PinSocket_1x12_P2.54mm_Vertical
J19: FrontPanel; IDC-Header_2x04_P2.54mm_Vertical
J20: I2C; PinSocket_1x05_P2.54mm_Vertical
L1: 100uH; L_Radial_D9.5mm_P5.00mm_Fastron_07HVP
Q1: BS250; TO-92_Inline_Wide
R1, R2, R6, R7, R16, R17, R18, R19, R20, R21, R22, R23, R24, R26, R27, R28, R29: 10k; R_Axial_DIN0207_L6.3mm_D2.5mm_P10.16mm_Horizontal
R3, R4, R5, R8, R25, R30, R31, R32, R33, R34, R35, R36: 100R; R_Axial_DIN0207_L6.3mm_D2.5mm_P10.16mm_Horizontal
R9: 12K; R_Axial_DIN0207_L6.3mm_D2.5mm_P10.16mm_Horizontal
R10: 1.2K; R_Axial_DIN0207_L6.3mm_D2.5mm_P10.16mm_Horizontal
R11, R12, R15: 4k7; R_Axial_DIN0207_L6.3mm_D2.5mm_P10.16mm_Horizontal
R13: 27k; R_Axial_DIN0207_L6.3mm_D2.5mm_P10.16mm_Horizontal
R14: 470R; R_Axial_DIN0207_L6.3mm_D2.5mm_P10.16mm_Horizontal
SW1: SW_SPST; SS-12D06L5
TP1: 12v; TestPoint_Pad_1.0x1.0mm
TP2: 14v; TestPoint_Pad_1.0x1.0mm
TP3: 5v; TestPoint_Pad_1.0x1.0mm
TP4: 3.3v; TestPoint_Pad_1.0x1.0mm
U1: AT24C04C-PUM; DIP-8_W7.62mm_Socket
U2: UT232A; DIP-16_W7.62mm_Socket
U3: LM2941T; TO-220-5_Horizontal_TabDown
U4: Pico; RPi_Pico_SMD_TH
U5: L78L33ACZTR; TO-92_Inline_Wide
U6: LM2576T-5; TO-220-5_Vertical
U7, U8: PCF8574; DIP-16_W7.62mm_Socket

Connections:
3.5-232-RX: J8.1, U2.13
3.5-232-TX: J8.3, U2.14
3v3: C1.2, C2.2, C15.1, C18.2, C19.1, C20.2, J3.10, J16.2, J16.4, J16.6, J16.8, J17.3, J19.3, J20.3, R1.1, R2.1, R6.1, R7.1, R11.1, R12.1, R16.1, R17.1, R22.1, R23.2, R24.1, R26.2, R27.2, R28.2, R29.1, TP4.1, U1.8, U2.16, U5.1, U7.16, U8.16
5v: C8.2, C14.1, C17.1, J3.9, J6.9, J10.6, J11.2, J17.4, J19.5, J20.4, L1.2, Q1.1, R14.2, TP3.1, U5.3, U6.4
12v: C16.1, J10.7, J18.11, J18.12, R13.1, SW1.2, TP1.1, U6.1
232-RX: J10.2, U2.8
232-TX: J10.3, U2.7
433TX: R8.2, U4.5
ACC-IO-1: R5.1, U8.4
ACC-IO-2: R4.1, U8.5
ACC-IO-3: R3.1, U8.6
ADC1: J17.6, U4.32
ADC2: J17.7, U4.34
BAT-MON: R13.2, R15.1, U4.31
EXPAN_IO1: J17.8, U7.11
EXPAN_IO2: J17.9, U7.10
EXPAN_IO3: J17.10, U7.9
FP_INT1: J19.1, R7.2, U4.15
FP_INT2: J19.2, R24.2, U4.9
GND: C1.1, C2.1, C5.1, C6.1, C8.1, C9.2, C10.2, C11.2, C12.2, C13.2, C14.2, C15.2, C16.2, C17.2, C18.1, C19.2, C20.1, D2.2, D3.2, D4.1, J3.5, J3.6, J3.7, J3.8, J6.10, J9.S, J10.0, J10.5, J11.1, J12.2, J13.1, J14.T, J15.T, J17.5, J18.1, J18.2, J19.7, J20.5, R10.2, R15.2, R18.1, R19.1, R20.1, R21.1, U1.1, U1.2, U1.3, U1.4, U1.7, U2.15, U3.2, U3.3, U4.3, U4.8, U4.13, U4.18, U4.23, U4.28, U4.33, U4.38, U5.2, U6.3, U6.5, U7.1, U7.3, U7.8, U8.2, U8.3, U8.8
IO-EXP1-INT: R26.1, U4.10, U7.13
IO-EXP2-INT: R28.1, U4.27, U8.13
LCD-LITE: J6.1, U7.12
LCD-RST: J6.8, U4.4
LED-DATA: J19.8, U4.14
MCU-UART0-RX: J8.9, U4.2
MCU-UART0-TX: J8.7, U4.1
MCU-UART1-RX: U2.9, U4.12
MCU-UART1-TX: U2.10, U4.11
unnamed: C3.1, U2.1
unnamed: C3.2, U2.3
unnamed: C4.1, U2.4
unnamed: C4.2, U2.5
unnamed: C5.2, U2.2
unnamed: C6.2, U2.6
unnamed: C9.1, C10.1, D5.1, U3.4
unnamed: C11.1, C12.1, D1.2, R9.1, TP2.1, U3.5
unnamed: C13.1, D1.1, D2.1, F1.1, SW1.1
unnamed: D3.1, L1.1, U6.2
unnamed: D4.2, R14.1
unnamed: D5.2, J12.1
unnamed: F1.2, J13.2
unnamed: J1.S, J4.2
unnamed: J1.T, J4.1
unnamed: J2.S, J4.5
unnamed: J2.T, J4.4
unnamed: J4.8, J7.T
unnamed: J4.9, J7.S
unnamed: J4.11, J5.T
unnamed: J4.12, J5.S
unnamed: J8.2, J9.R
unnamed: J8.4, J9.T
unnamed: J8.5, J9.RN
unnamed: J8.6, J9.TN
unnamed: J10.4, R2.2, R4.2
unnamed: J10.8, R1.2, R3.2
unnamed: J10.9, R5.2, R6.2
unnamed: J11.3, R8.1
unnamed: J14.R, R22.2, R32.1
unnamed: J14.S, R29.2, R33.1
unnamed: J15.R, R17.2, R30.1
unnamed: J15.S, R16.2, R31.1
unnamed: J16.1, R18.2, U7.4
unnamed: J16.3, R19.2, U7.5
unnamed: J16.5, R20.2, U7.6
unnamed: J16.7, R21.2, U7.7
unnamed: Q1.2, U4.40
unnamed: Q1.3, U4.39
unnamed: R9.2, R10.1, U3.1
unnamed: R23.1, U7.2
unnamed: R25.2, U4.16
unnamed: R27.1, U8.1
unnamed: R30.2, U8.9
unnamed: R31.2, U8.10
unnamed: R32.2, U8.11
unnamed: R33.2, U8.12
unnamed: R34.2, U4.17
unnamed: R35.2, U4.19
unnamed: R36.2, U4.20
OUTPUT-CS: J3.4, R34.1
OUTPUT-MISO: J3.2, R25.1
OUTPUT-MOSI: J3.1, R36.1
OUTPUT-SCK: J3.3, R35.1
SCL: J3.11, J17.2, J19.6, J20.1, R12.2, U1.6, U4.7, U7.14, U8.14
SDA: J3.12, J17.1, J19.4, J20.2, R11.2, U1.5, U4.6, U7.15, U8.15
SPI-CS-LCD: J6.5, U4.22
SPI-CS-SD: J6.6, U4.29
SPI-DC: J6.7, U4.26
SPI-MISO: J6.2, U4.21
SPI-MOSI: J6.4, U4.25
SPI-SCK: J6.3, U4.24
TTL-SER-0-RX: J8.10, U2.12
TTL-SER-0-TX: J8.8, U2.11

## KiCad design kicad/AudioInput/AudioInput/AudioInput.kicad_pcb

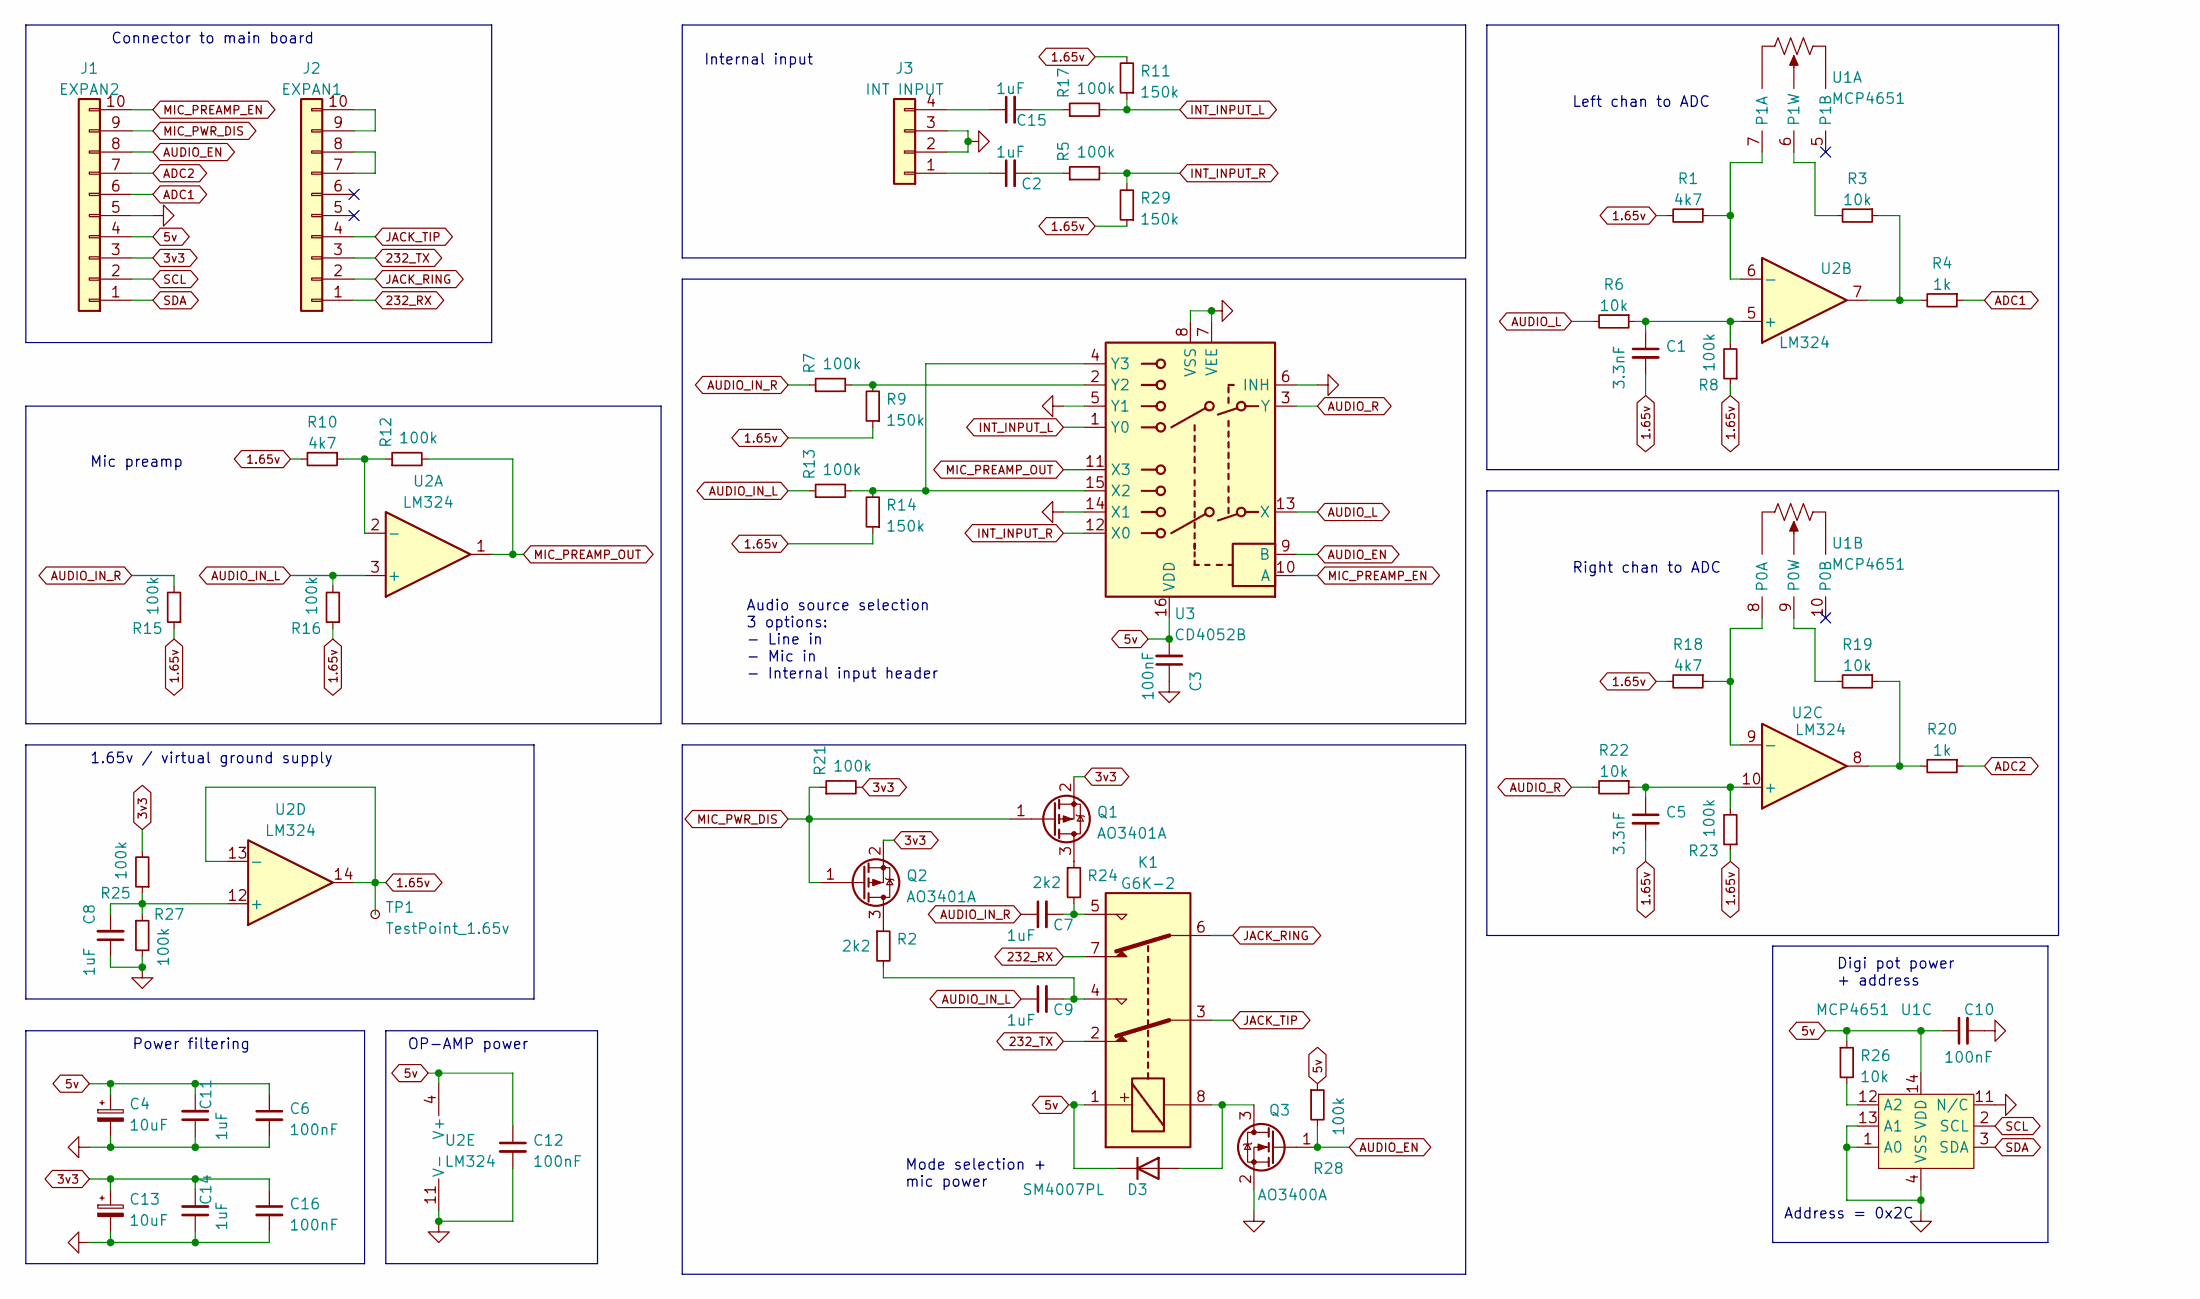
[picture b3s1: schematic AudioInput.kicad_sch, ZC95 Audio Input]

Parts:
C1, C5: 3.3nF; C_0603_1608Metric_Pad1.08x0.95mm_HandSolder; LCSC C1613
C2, C7, C8, C9, C11, C14, C15: 1uF; C_0603_1608Metric_Pad1.08x0.95mm_HandSolder; LCSC C15849
C3, C6, C10, C12, C16: 100nF; C_0603_1608Metric_Pad1.08x0.95mm_HandSolder; LCSC C14663
C4, C13: 10uF; C_0603_1608Metric_Pad1.08x0.95mm_HandSolder; LCSC C19702
D3: SM4007PL; D_SOD-123F; LCSC C64898
J1: EXPAN2; PinHeader_1x10_P2.54mm_Vertical
J2: EXPAN1; PinHeader_1x10_P2.54mm_Vertical
J3: INT INPUT; PinHeader_1x04_P2.54mm_Vertical
K1: G6K-2; Relay_DPDT_Omron_G6K-2F-Y; LCSC C47190
Q1, Q2: AO3401A; SOT-23; LCSC C15127
Q3: AO3400A; SOT-23; LCSC C20917
R1, R10, R18: 4k7; R_0603_1608Metric_Pad0.98x0.95mm_HandSolder; LCSC C23162
R2, R24: 2k2; R_0603_1608Metric_Pad0.98x0.95mm_HandSolder; LCSC C4190
R3, R6, R19, R22, R26: 10k; R_0603_1608Metric_Pad0.98x0.95mm_HandSolder; LCSC C25804
R4, R20: 1k; R_0603_1608Metric_Pad0.98x0.95mm_HandSolder; LCSC C21190
R5, R7, R8, R12, R13, R15, R16, R17, R21, R23, R25, R27, R28: 100k; R_0603_1608Metric_Pad0.98x0.95mm_HandSolder; LCSC C25803
R9, R11, R14, R29: 150k; R_0603_1608Metric_Pad0.98x0.95mm_HandSolder; LCSC C22807
TP1: TestPoint_1.65v; TestPoint_Pad_D1.5mm
U1: MCP4651; TSSOP-14_4.4x5mm_P0.65mm; LCSC C148010
U2: LM324; SOIC-14_3.9x8.7mm_P1.27mm; LCSC C71035
U3: CD4052B; SOIC-16_3.9x9.9mm_P1.27mm; LCSC C6521

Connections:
1.65v: C1.2, C5.2, R1.2, R8.1, R9.1, R10.2, R11.2, R14.1, R15.1, R16.1, R18.2, R23.1, R29.1, TP1.1, U2.13 (-), U2.14
3v3: C13.1, C14.2, C16.1, J1.3, Q1.2 (S), Q2.2 (S), R21.2, R25.2
5v: C3.2, C4.1, C6.1, C10.1, C11.2, C12.1, D3.1 (K), J1.4, K1.1, R26.1, R28.1, U1.14 (VDD), U2.4 (V+), U3.16 (VDD)
232_RX: J2.1, K1.7
232_TX: J2.3, K1.2
ADC1: J1.6, R4.1
ADC2: J1.7, R20.1
AUDIO_EN: J1.8, Q3.1 (G), R28.2, U3.9 (B)
AUDIO_IN_L: C9.1, R13.1, R16.2, U2.3 (+)
AUDIO_IN_R: C7.1, R7.1, R15.2
AUDIO_L: R6.2, U3.13 (X)
AUDIO_R: R22.2, U3.3 (Y)
GND: C3.1, C4.2, C6.2, C8.1, C10.2, C11.1, C12.2, C13.2, C14.1, C16.2, J1.5, J3.2, J3.3, Q3.2 (S), R27.2, U1.1 (A0), U1.4 (VSS), U1.11 (N/C), U1.13 (A1), U2.11 (V-), U3.5 (Y1), U3.6 (INH), U3.7 (VEE), U3.8 (VSS), U3.14 (X1)
INT_INPUT_L: R11.1, R17.2, U3.1 (Y0)
INT_INPUT_R: R5.2, R29.2, U3.12 (X0)
JACK_RING: J2.2, K1.6
JACK_TIP: J2.4, K1.3
MIC_PREAMP_EN: J1.10, U3.10 (A)
MIC_PREAMP_OUT: R12.2, U2.1, U3.11 (X3)
MIC_PWR_DIS: J1.9, Q1.1 (G), Q2.1 (G), R21.1
unnamed: C1.1, R6.1, R8.2, U2.5 (+)
unnamed: C2.2, R5.1
unnamed: C15.1, J3.4
unnamed: C15.2, R17.1
unnamed: D3.2 (A), K1.8, Q3.3 (D)
unnamed: J2.7, J2.8
unnamed: J2.9, J2.10
unnamed: C2.1, J3.1
unnamed: C9.2, K1.4, R2.2
unnamed: C7.2, K1.5, R24.2
unnamed: R1.1, U1.7 (P1A), U2.6 (-)
unnamed: Q2.3 (D), R2.1
unnamed: R3.1, R4.2, U2.7
unnamed: R3.2, U1.6 (P1W)
unnamed: R7.2, R9.2, U3.2 (Y2)
unnamed: Q1.3 (D), R24.1
unnamed: R18.1, U1.8 (P0A), U2.9 (-)
unnamed: R19.2, U1.9 (P0W)
unnamed: R26.2, U1.12 (A2)
unnamed: R10.1, R12.1, U2.2 (-)
unnamed: R19.1, R20.2, U2.8
unnamed: C5.1, R22.1, R23.2, U2.10 (+)
unnamed: C8.2, R25.1, R27.1, U2.12 (+)
unnamed: R13.2, R14.2, U3.4 (Y3), U3.15 (X2)
SCL: J1.2, U1.2 (SCL)
SDA: J1.1, U1.3 (SDA)

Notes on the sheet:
Digi pot power + address
Mode selection + mic power
Internal input
Right chan to ADC
Address = 0x2C
1.65v / virtual ground supply
Mic preamp
OP-AMP power
Connector to main board
Power filtering
Audio source selection 3 options: - Line in - Mic in - Internal input header
Left chan to ADC

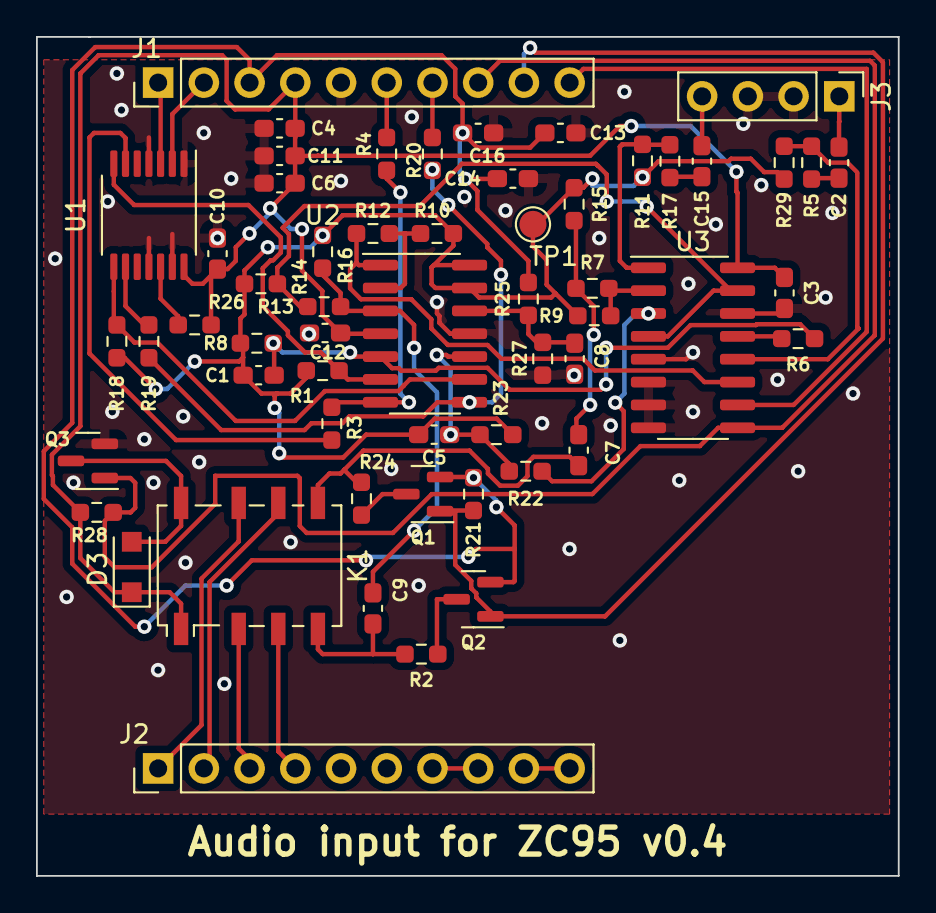
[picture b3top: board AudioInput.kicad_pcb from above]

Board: 2 copper layers, 47.9 x 46.6 mm, 57 parts (0 on the bottom side), 46 nets.
